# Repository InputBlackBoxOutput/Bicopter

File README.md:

# Bicopter
A bicopter is a type of unmanned aerial vehicle that features two rotors for generating lift and controlling its movement. Unlike traditional quadcopters, which have four rotors, bicopters use only two rotors to achieve flight.

## Assembly
- Uses a PCB that acts at the frame and provides support to all the other components.
- Two motors each connected to a servo motor using a 3D-printed contraption
- The propellers have a mounting boss with a hole diameter equal to the motor shaft diameter
- The servos are attached to the PCB using strong glue 
- The rechargeable lithium-ion (Li-ion) battery is mounted under the PCB using zip ties
- The landing gears are 3D printed and attached to the PCB using screws and nuts

## Hardware block diagram
- ESP32 WROOM: 
	- Control BLDC and servo motors to maintain flight
	- Communicate with the remote controller
- BLDC motor: Provide lift
- Servo motor: Tilt BLDC motors to move the craft
- LED: 
	- Help locate the craft in the dark
	- Indicate battery voltage level 
- LiPo battery + BMS: 
	- Charge the battery 
	- Check battery voltage level
	- Perform power conversion

## Application Interface Screenshot
- Connect to the bicopter
- Send flight control information
- Receive and display battery and communication strength information

### Made with lots of ⏱️, 📚 and ☕ by InputBlackBoxOutput

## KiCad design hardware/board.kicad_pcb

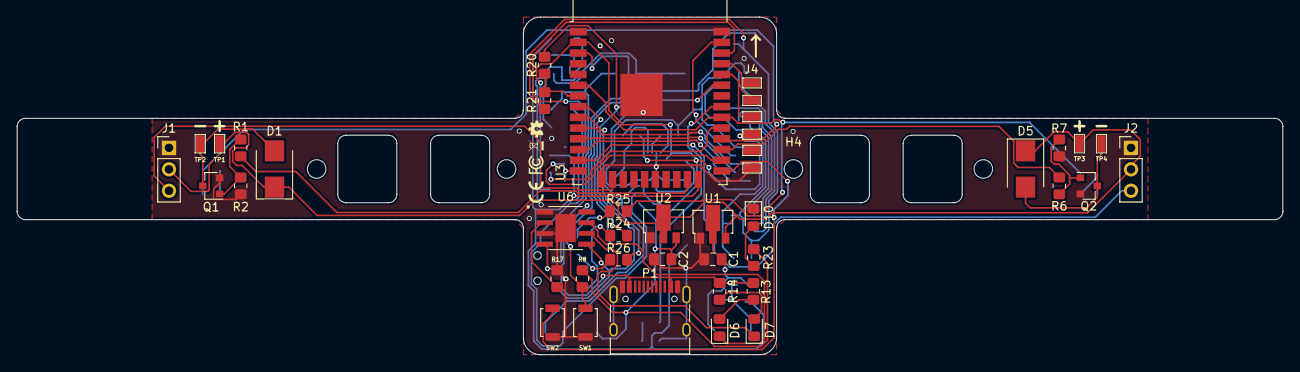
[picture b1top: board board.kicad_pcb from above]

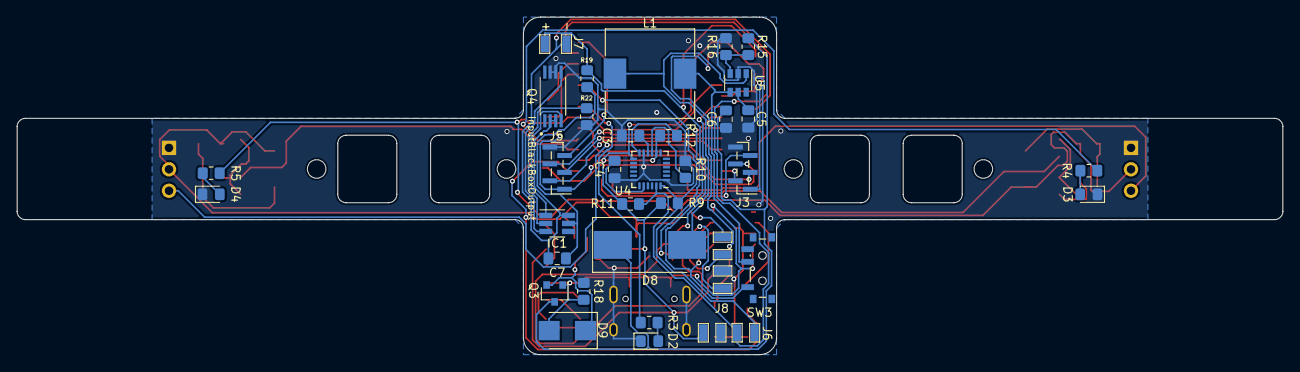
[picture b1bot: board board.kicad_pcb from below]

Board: 2 copper layers, 150.0 x 40.0 mm, 75 parts (34 on the bottom side), 59 nets.

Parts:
C1, C2: 10uF; C_0805_2012Metric_Pad1.18x1.45mm_HandSolder
C3, C7: 0.1uF; C_0805_2012Metric_Pad1.18x1.45mm_HandSolder
C4: 2.2nF; C_0805_2012Metric_Pad1.18x1.45mm_HandSolder
C5, C6: 22uF; C_0805_2012Metric_Pad1.18x1.45mm_HandSolder
D1, D5: SS-12; D_SMB
D2, D3, D4, D10: LED; LED_0805_2012Metric_Pad1.15x1.40mm_HandSolder
D6: LED-RED; LED_0805_2012Metric_Pad1.15x1.40mm_HandSolder
D7: LED-BLUE; LED_0805_2012Metric_Pad1.15x1.40mm_HandSolder
D8: SS34; D_SMC_Handsoldering
D9: SS14; D_SMB
H1, H2, H3, H4: MountingHole; MountingHole_2.2mm_M2
IC1: DW01A; SOT-23-6_Handsoldering
J1, J2: Conn_01x03_Male; PinHeader_1x03_P2.54mm_Vertical
J3, J5: Conn_01x06; PinHeader_1x06_P1.00mm_Vertical_SMD_Pin1Left
J4: Conn_01x06_Female; Wire-Pad-01x06
J6, J8: Conn_01x04; Wire-Pad-01x04
J7: Conn_01x02; Wire-Pad-01x02
L1: 22uH; L_10.4x10.4_H4.8
P1: USB_C_Plug_USB2.0; USB_C_Receptacle_HRO_TYPE-C-31-M-12
Q1, Q2: AO3400A; SOT-23
Q3: AO3401A; SOT-23
Q4: FS8205A; SOP65P640X120-8N
R1, R6, R19, R24: 100R; R_0805_2012Metric_Pad1.20x1.40mm_HandSolder
R2, R7, R8, R9, R11, R12, R18, R20, R21: 10k; R_0805_2012Metric_Pad1.20x1.40mm_HandSolder
R3, R4, R5, R13, R14, R16, R22, R23, R25, R26: 1k; R_0805_2012Metric_Pad1.20x1.40mm_HandSolder
R10: 4.7k; R_0805_2012Metric_Pad1.20x1.40mm_HandSolder
R15: 7.5k; R_0805_2012Metric_Pad1.20x1.40mm_HandSolder
R17: 1.2k; R_0805_2012Metric_Pad1.20x1.40mm_HandSolder
SW1, SW2: SW_Push; SW_SPST_B3U-1000P
SW3: SW_SPST; SW_SPDT_PCM12
TP1: A+; Wire-Pad
TP2: A-; Wire-Pad
TP3: B+; Wire-Pad
TP4: B-; Wire-Pad
U1: HT7850-1-SOT89; SOT-89-3
U2: HT7833-1-SOT89; SOT-89-3
U3: ESP32-WROOM-32
U4: MPU-6050; InvenSense_QFN-24_4x4mm_P0.5mm
U5: MT3608; SOT-23-6
U6: TP4056; SOP127P600X175-9N

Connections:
+3V3: C2.1, J3.1, J4.4, J5.1, J6.4, R8.1, R9.1, R11.1, R12.1, R23.1, U2.3, U3.2, U4.8, U4.13
+5V: D1.1, D5.1, J1.2, J2.2, TP1.1, TP3.1, U1.3, U2.2
/ADC: R20.2, R21.1, U3.7
/EN: R8.2, SW1.1, U3.3
/IO0: SW2.1, U3.25
/IO2: J3.5, U3.24
/IO4: J3.4, U3.26
/IO5: J3.3, U3.29
/IO12: J3.2, U3.14
/IO23: J5.5, U3.37
/IO25: J5.4, U3.10
/IO26: J5.3, U3.11
/IO27: J5.2, U3.12
/LED_A: R4.1, U3.28
/LED_B: R5.1, R25.2, U3.6, U3.30
/LED_G: R26.2, U3.9
/LED_R: R24.2, U3.8
/LED_TAIL: R3.1, U3.31
/MOTOR_A: R1.2, U3.23
/MOTOR_B: R6.2, U3.27
/RXD: J4.3, U3.34
/SCL: J6.2, R11.2, U3.36, U4.23
/SDA: J6.1, R9.2, U3.33, U4.24
/SERVO_A: J1.3, U3.16
/SERVO_B: J2.3, U3.13
/Sheet6241753E/BATT+: J7.1, R19.1, R20.1, SW3.1, U6.5
/Sheet6241753E/BATT+_OUT: C6.1, D8.1, Q3.3, R15.1
/Sheet6241753E/BATT-: C7.2, IC1.6, J7.2, Q4.2, Q4.3, R21.2
/Sheet6241753E/CHRG: D6.1, U6.7
/Sheet6241753E/STDBY: D7.1, U6.6
/Sheet6241753E/VBUS: D9.2, P1.A4, P1.A9, P1.B4, P1.B9, Q3.1, R13.1, R14.1, R18.1, U6.4, U6.8
/TXD: J4.2, U3.35
GND: C1.2, C2.2, C3.2, C4.2, C5.2, C6.2, D2.1, D3.1, D4.1, D10.1, J1.1, J2.1, J3.6, J4.6, J5.6, J6.3, J8.2, P1.A1, P1.A12, P1.B1, P1.B12, P1.S1, Q1.2, Q2.2, Q4.6, Q4.7, R2.2, R7.2, R10.2, R16.2, R17.2, R18.2, R22.1, SW1.2, SW2.2, U1.1, U2.1, U3.1, U3.15, U3.38, U3.39, U4.1, U4.11, U4.18, U5.2, U6.1, U6.3, U6.9
unnamed: C3.1, U4.10
unnamed: C4.1, U4.20
unnamed: C5.1, L1.1, SW3.2, U5.4, U5.5
unnamed: C7.1, IC1.5, R19.2
unnamed: D1.2, Q1.3, TP2.1
unnamed: D2.2, R3.2
unnamed: D3.2, R4.2
unnamed: D4.2, R5.2
unnamed: D5.2, Q2.3, TP4.1
unnamed: D6.2, R13.2
unnamed: D7.2, R14.2
unnamed: D8.2, L1.2, U5.1
unnamed: D10.2, R23.2
unnamed: IC1.1, Q4.4
unnamed: IC1.2, R22.2
unnamed: IC1.3, Q4.5
unnamed: J8.1, R24.1
unnamed: J8.3, R26.1
unnamed: J8.4, R25.1
unnamed: Q1.1, R1.1, R2.1
unnamed: Q2.1, R6.1, R7.1
unnamed: R10.1, U4.9
unnamed: R12.2, U4.12
unnamed: R15.2, R16.1, U5.3
unnamed: R17.1, U6.2
VCC: C1.1, D9.1, Q3.2, U1.2

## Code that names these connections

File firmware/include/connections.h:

// Peripheral connections

#define LED_TAIL_PIN 19
#define LED_A_PIN 17
#define LED_B_PIN 18

#define RGB_LED_R_PIN 32
#define RGB_LED_G_PIN 33
#define RGB_LED_B_PIN 34

#define MOTOR_A_PIN 15
#define MOTOR_B_PIN 16

#define SERVO_A_PIN 13
#define SERVO_B_PIN 14

#define BATT_ADC_PIN 35

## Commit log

2022-03-19 Schematics added
2022-03-19 PCB layout
2022-03-20 PCB routed
2022-04-16 Firmware files added
2022-04-18 PCB: Mounting holes for landing gear
2022-04-29 File added: README.md
2022-04-30 Documents added
2022-04-30 README: Images added
2022-05-02 Models of 3D printed parts added
2022-05-02 PCB: Holes for LiPo battery zip tie added
2022-05-03 Windows application files added
2022-05-05 PCB: CE, FCC, WEEE and OSHW markings added
2022-05-05 PCB: Fixed connection to ground plane
2022-05-07 Firmware: LED
2022-05-07 Firmware: Servo motor + BLDC motor
2022-05-10 Firmware: IMU
2022-05-18 Electron application UI
2022-05-22 Electron application: Connect over WiFi
2022-05-25 Electron application: Button controls
2022-05-25 Electron application: Message modal
2022-06-20 Electron application: Adapt to small screen devices
2022-06-20 Electron application: Minor changes
2022-06-23 Electron application: Files added
2022-06-25 Electron application: Help & About
2022-07-04 Folder reorganized: hardware
2022-07-04 PCB: Minor changes
2022-07-10 3D printed parts: STL files
2022-07-31 README: Interface screenshot added
2022-10-10 Minor changes
2022-10-13 Firmware: BMS
2022-10-28 Firmware: State
2022-10-28 Firmware: Server
2022-10-29 Firmware: PID
2022-10-29 Application: WiFi strength + Battery voltage stats
2022-11-26 File created: LICENSE
2023-09-30 README: Info added
